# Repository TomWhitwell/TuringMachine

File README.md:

# TuringMachine Mark 2

Since it was launched in June 2012, the Turing Machine has become one of the most popular Eurorack DIY projects. It is a random looping sequencer that spits out basslines and melodies. It generates strings of random voltages that can be locked into looping sequences. 
These sequences can be allowed to slip, changing gradually over time. This module was inspired by the long history of shift register pseudorandom synth circuits, including the Triadex Muse, Buchla 266 Source of Uncertainly and Grant Richter’s Noisering.

[This video explains how the Turing Machine works.](https://www.youtube.com/watch?v=Le26BIqB8Y8)  

The 2016 revised Turing Machine has many improvements:  
- Rotary loop length switch 
- Pulse out
- Two boards, includes Backpack circuit to drive expanders (compatible with old Music Thing expanders)  
- Easier to build: a larger PCB in the same width, clock and noise circuits are more robust
- Noise level trimmer & reduced voltage in noise circuit to make circuit more robust with different noise transistors 
- Compatible with existing expanders 

*“I am interested in perceptible processes. I want to be able to hear the process happening throughout the music. To facilitate closely detailed listening a musical process should happen extremely gradually.”* Steve Reich, [Music as a Gradual Process](http://www.bussigel.com/systemsforplay/wp-content/uploads/2014/02/Reich_Gradual-Process.pdf), 1968. 

[Schematic](https://github.com/TomWhitwell/TuringMachine/blob/master/Collateral/PDF%20Schematics/TuringMachine2_Schematic_May2016.pdf)

Status:   
April 2016: Design files and Gerbers tested and prototyped successfully 

License:  
[CC-BY-SA](https://creativecommons.org/licenses/by-sa/3.0/)

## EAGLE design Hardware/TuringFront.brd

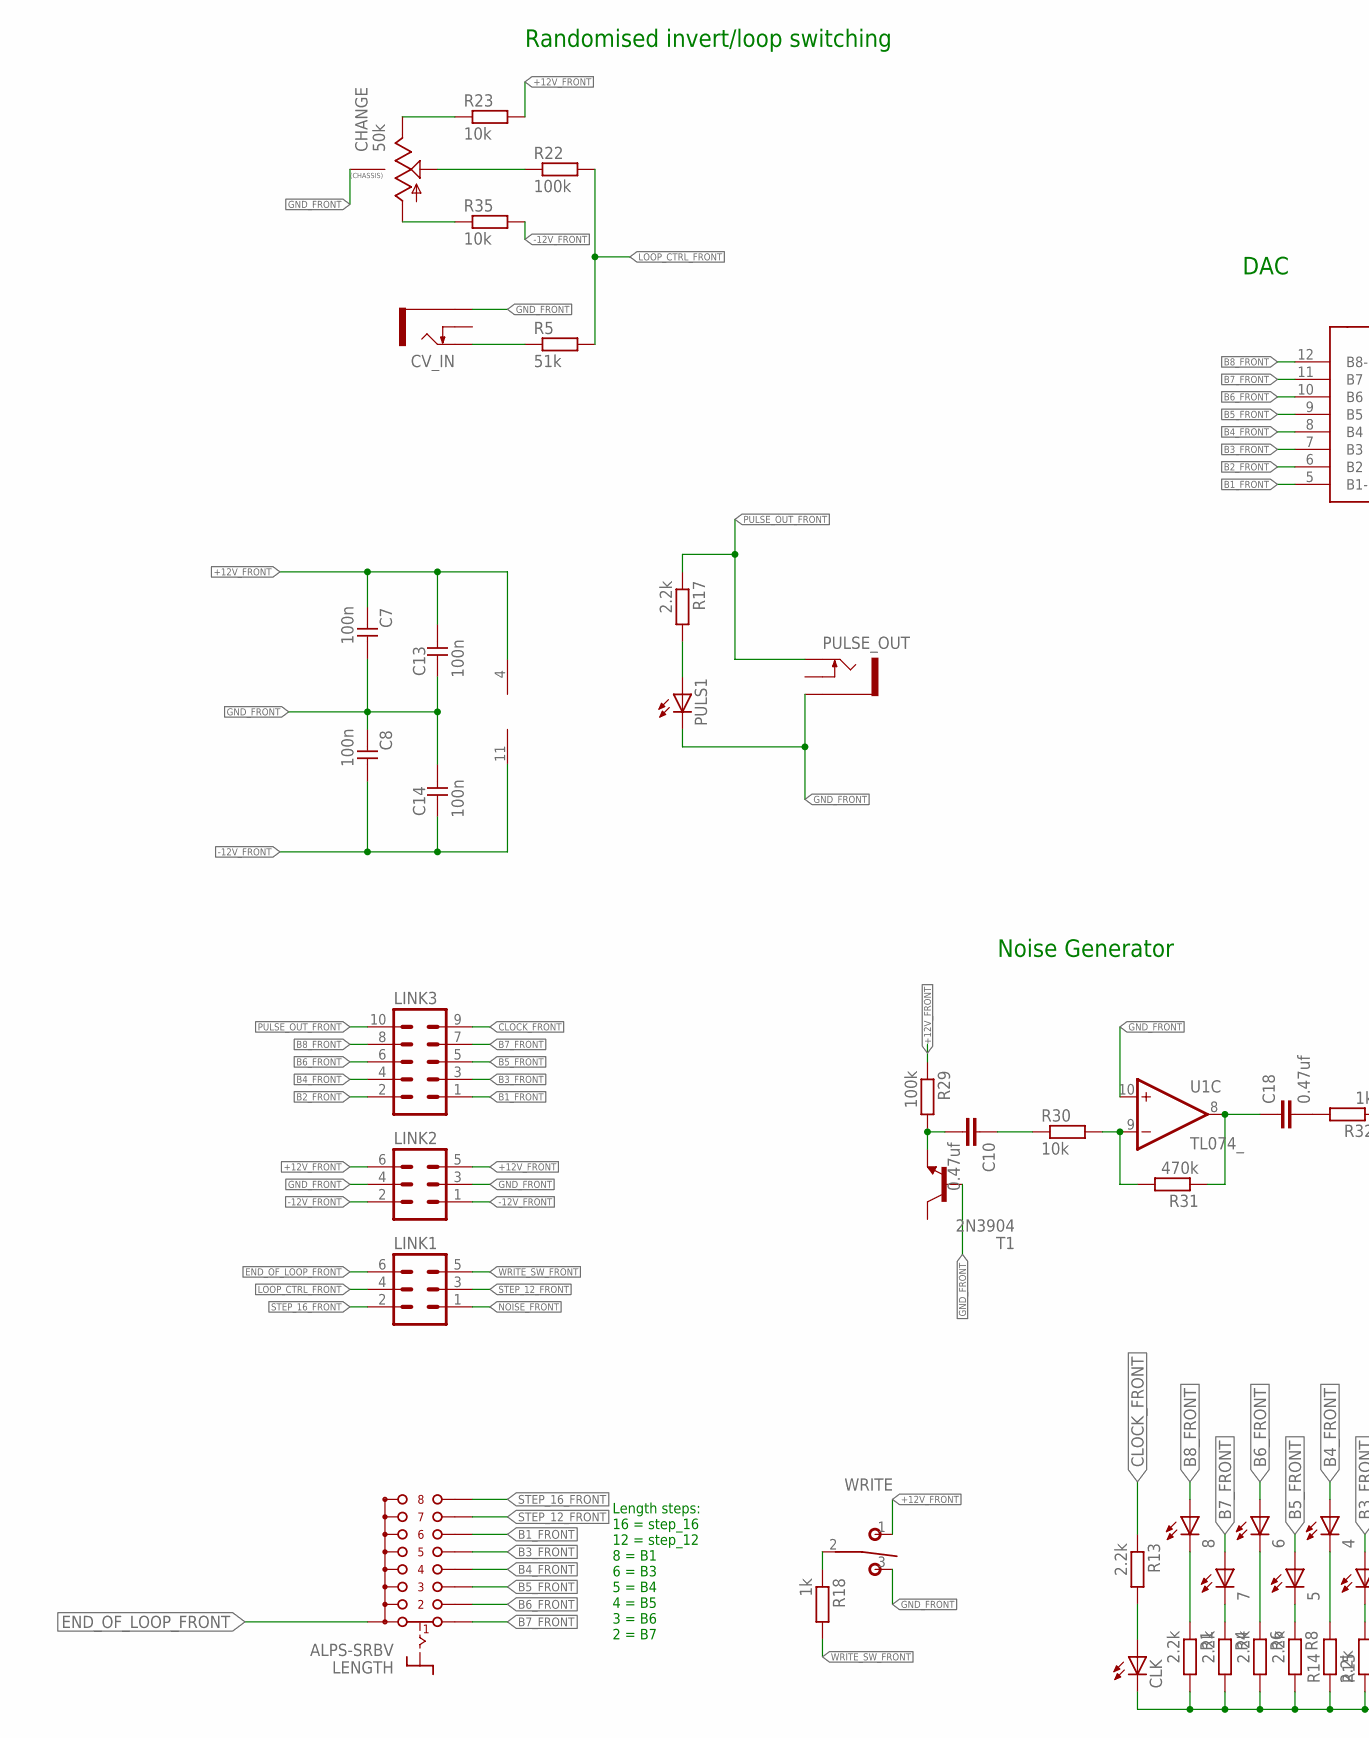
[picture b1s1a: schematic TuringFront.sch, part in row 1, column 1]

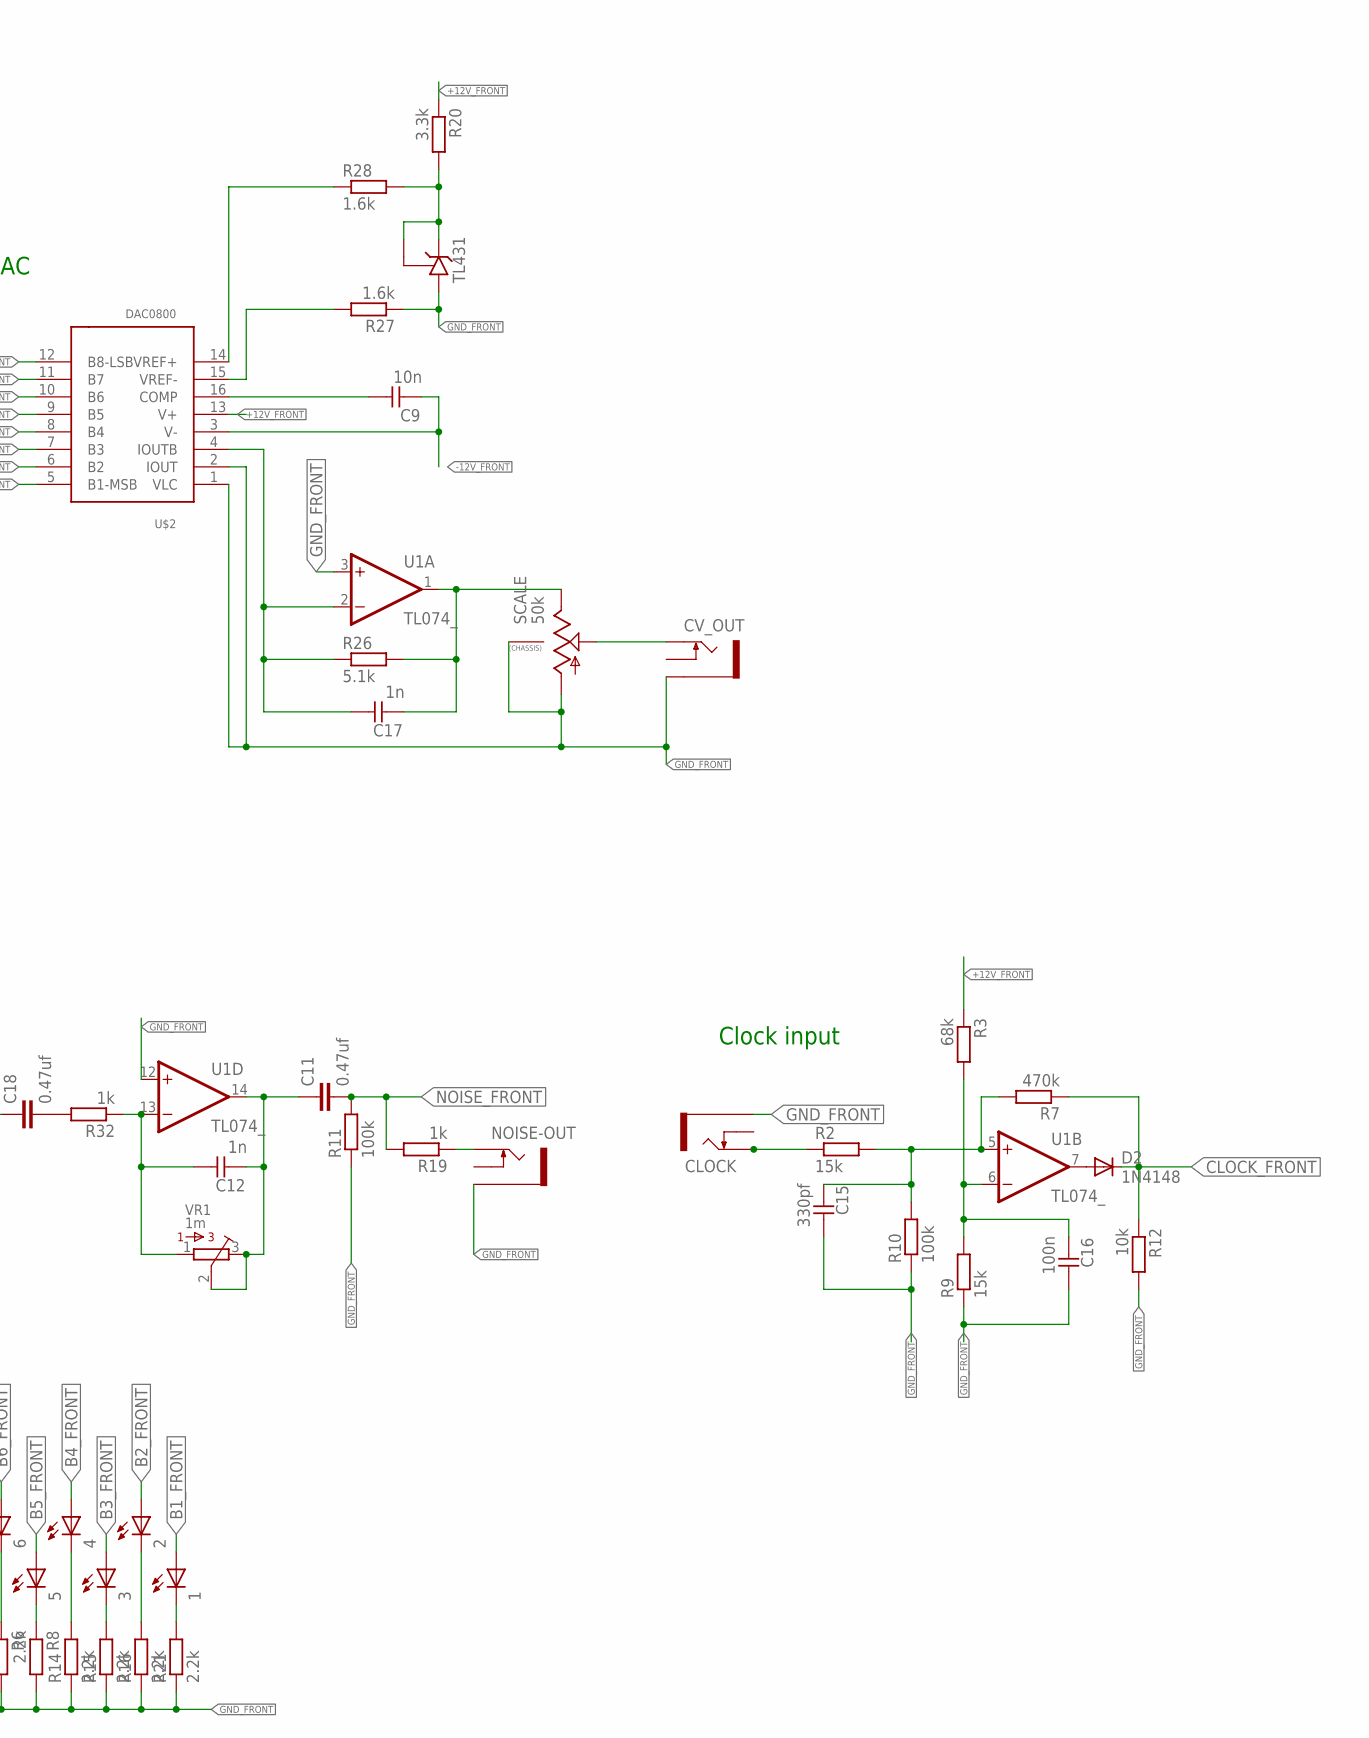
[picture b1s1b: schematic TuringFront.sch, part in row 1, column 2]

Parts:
1, 2, 3, 4, 5, 6, 7, 8: LED3MM
C7, C8, C13, C14, C16: 100n; C050-024X044
C9: 10n; C050-024X044
C10, C11, C18: 0.47uf; C050-035X075
C12, C17: 1n; C050-024X044
C15: 330pf; C050-024X044
CHANGE: 50k; 9MM_SNAP-IN_POT
CLK: LED3MM
CLOCK: THONKICONNNEW; WQP-PJ301M-12_JACK
CV_IN: THONKICONNNEW; WQP-PJ301M-12_JACK
CV_OUT: THONKICONNNEW; WQP-PJ301M-12_JACK
D2: 1N4148; DO35-7
LENGTH: ALPS-SRBV
LINK1, LINK2: MA03-2BACKSIDE
LINK3: 10PIN_BACKSIDE
NOISE-OUT: THONKICONNNEW; WQP-PJ301M-12_JACK
PULS1: LED3MM
PULSE_OUT: THONKICONNNEW; WQP-PJ301M-12_JACK
R1, R4, R6, R8, R13, R14, R15, R16, R17, R21: 2.2k; 0207/7
R2, R9: 15k; 0207/7
R3: 68k; 0207/7
R5: 51k; 0207/7
R7, R31: 470k; 0207/7
R10, R22, R29: 100k; 0207/7
R11: 100k; 7MM_RESISTOR
R12, R23, R30, R35: 10k; 0207/7
R18, R19, R32: 1k; 0207/7
R20: 3.3k; 0207/7
R26: 5.1k; 0207/7
R27, R28: 1.6k; 0207/7
SCALE: 50k; 9MM_SNAP-IN_POT
T1: 2N3904; TO92
TL431: TL431CLP; TO92-CLP
U1: TL074_; DIL14
U$2: DAC0800; DIL16
VR1: 1m; BOURNS_3362P_TRIMMER
WRITE: T-80-T-SPDT-ON-OFF-ON; M9040P

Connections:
+12V_FRONT: C7.2, C13.1, LINK2.5, LINK2.6, R3.1, R20.1, R23.2, R29.1, U1.4 (V+), U$2.13 (V+), WRITE.1 (O)
-12V_FRONT: C8.1, C9.2, C14.2, LINK2.1, LINK2.2, R35.2, U1.11 (V-), U$2.3 (V-)
B1_FRONT: 1.A, LENGTH.F (6), LINK3.1, U$2.5 (B1-MSB)
B2_FRONT: 2.A, LINK3.2, U$2.6 (B2)
B3_FRONT: 3.A, LENGTH.E (5), LINK3.3, U$2.7 (B3)
B4_FRONT: 4.A, LENGTH.D (4), LINK3.4, U$2.8 (B4)
B5_FRONT: 5.A, LENGTH.C (3), LINK3.5, U$2.9 (B5)
B6_FRONT: 6.A, LENGTH.B (2), LINK3.6, U$2.10 (B6)
B7_FRONT: 7.A, LENGTH.A (1), LINK3.7, U$2.11 (B7)
B8_FRONT: 8.A, LINK3.8, U$2.12 (B8-LSB)
CLOCK_FRONT: D2.C, LINK3.9, R7.1, R12.1, R13.1
END_OF_LOOP_FRONT: LENGTH.COM (A), LENGTH.COM2 (A), LINK1.6
GND_FRONT: C7.1, C8.2, C13.2, C14.1, C15.1, C16.1, CHANGE.CHASSIS2, CLK.K (C), CLOCK.P$3_SLEEVE (SLEEVE), CV_IN.P$3_SLEEVE (SLEEVE), CV_OUT.P$3_SLEEVE (SLEEVE), LINK2.3, LINK2.4, NOISE-OUT.P$3_SLEEVE (SLEEVE), PULS1.K (C), PULSE_OUT.P$3_SLEEVE (SLEEVE), R1.2, R4.2, R6.2, R8.2, R9.1, R10.1, R11.1, R12.2, R14.1, R15.1, R16.1, R21.1, R27.1, SCALE.1 (A), SCALE.CHASSIS2, T1.2 (B), TL431.A, U1.3 (+IN), U1.10 (+IN), U1.12 (+IN), U$2.1 (VLC), U$2.2 (IOUT), WRITE.3 (S)
LOOP_CTRL_FRONT: LINK1.4, R5.2, R22.2
MAIN_OUT: C17.2, R26.2, SCALE.3 (E), U1.1 (OUT)
unnamed: CLOCK.P$1_TIP (TIP), R2.1
unnamed: CV_IN.P$1_TIP (TIP), R5.1
unnamed: C15.2, R2.2, R7.2, R10.2, U1.5 (+IN)
unnamed: PULS1.A, R17.2
unnamed: D2.A, U1.7 (OUT)
unnamed: C18.2, R32.2
unnamed: R18.1, WRITE.2
unnamed: C16.2, R3.2, R9.2, U1.6 (-IN)
unnamed: C17.1, R26.1, U1.2 (-IN), U$2.4 (IOUTB)
unnamed: CLK.A, R13.2
unnamed: C10.2, R29.2, T1.3 (E)
unnamed: R20.2, R28.2, TL431.C, TL431.R
unnamed: C10.1, R30.1
unnamed: R30.2, R31.2, U1.9 (-IN)
unnamed: C18.1, R31.1, U1.8 (OUT)
unnamed: R27.2, U$2.15 (VREF-)
unnamed: C9.1, U$2.16 (COMP)
unnamed: R28.1, U$2.14 (VREF+)
unnamed: C12.1, R32.1, U1.13 (-IN), VR1.1
unnamed: 8.K (C), R1.1
unnamed: 7.K (C), R4.1
unnamed: 6.K (C), R6.1
unnamed: 5.K (C), R8.1
unnamed: 4.K (C), R14.2
unnamed: 3.K (C), R15.2
unnamed: 2.K (C), R16.2
unnamed: 1.K (C), R21.2
unnamed: CV_OUT.P$1_TIP (TIP), SCALE.2 (S)
unnamed: NOISE-OUT.P$1_TIP (TIP), R19.1
unnamed: C11.1, C12.2, U1.14 (OUT), VR1.2, VR1.3
unnamed: CHANGE.2 (S), R22.1
unnamed: CHANGE.3 (E), R23.1
unnamed: CHANGE.1 (A), R35.1
NOISE_FRONT: C11.2, LINK1.1, R11.2, R19.2
PULSE_OUT_FRONT: LINK3.10, PULSE_OUT.P$1_TIP (TIP), R17.1
STEP_12_FRONT: LENGTH.G (7), LINK1.3
STEP_16_FRONT: LENGTH.H (8), LINK1.2
WRITE_SW_FRONT: LINK1.5, R18.2

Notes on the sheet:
Randomised invert/loop switching
Length steps: 16 = step_16 12 = step_12 8 = B1 6 = B3 5 = B4 4 = B5 3 = B6 2 = B7
Noise Generator
Clock input
DAC

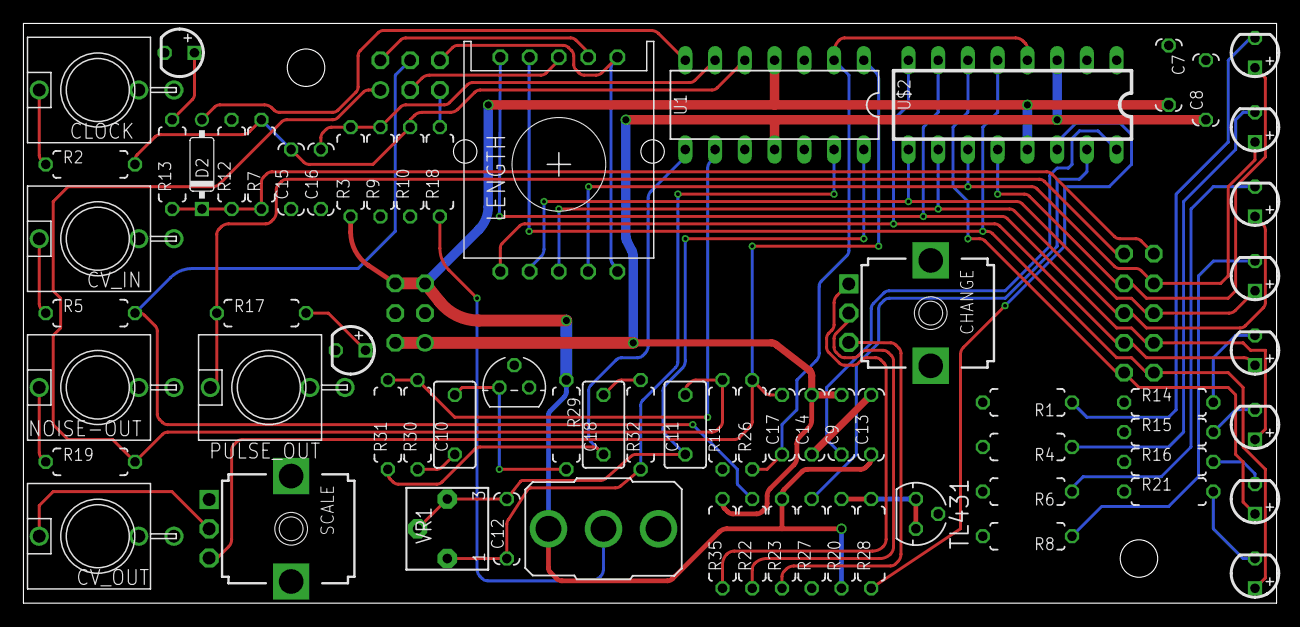
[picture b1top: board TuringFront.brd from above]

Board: 4 copper layers, 107.0 x 49.5 mm, 73 parts (0 on the bottom side), 53 nets.

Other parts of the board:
U$4, U$5: MOUNTING_HOLE

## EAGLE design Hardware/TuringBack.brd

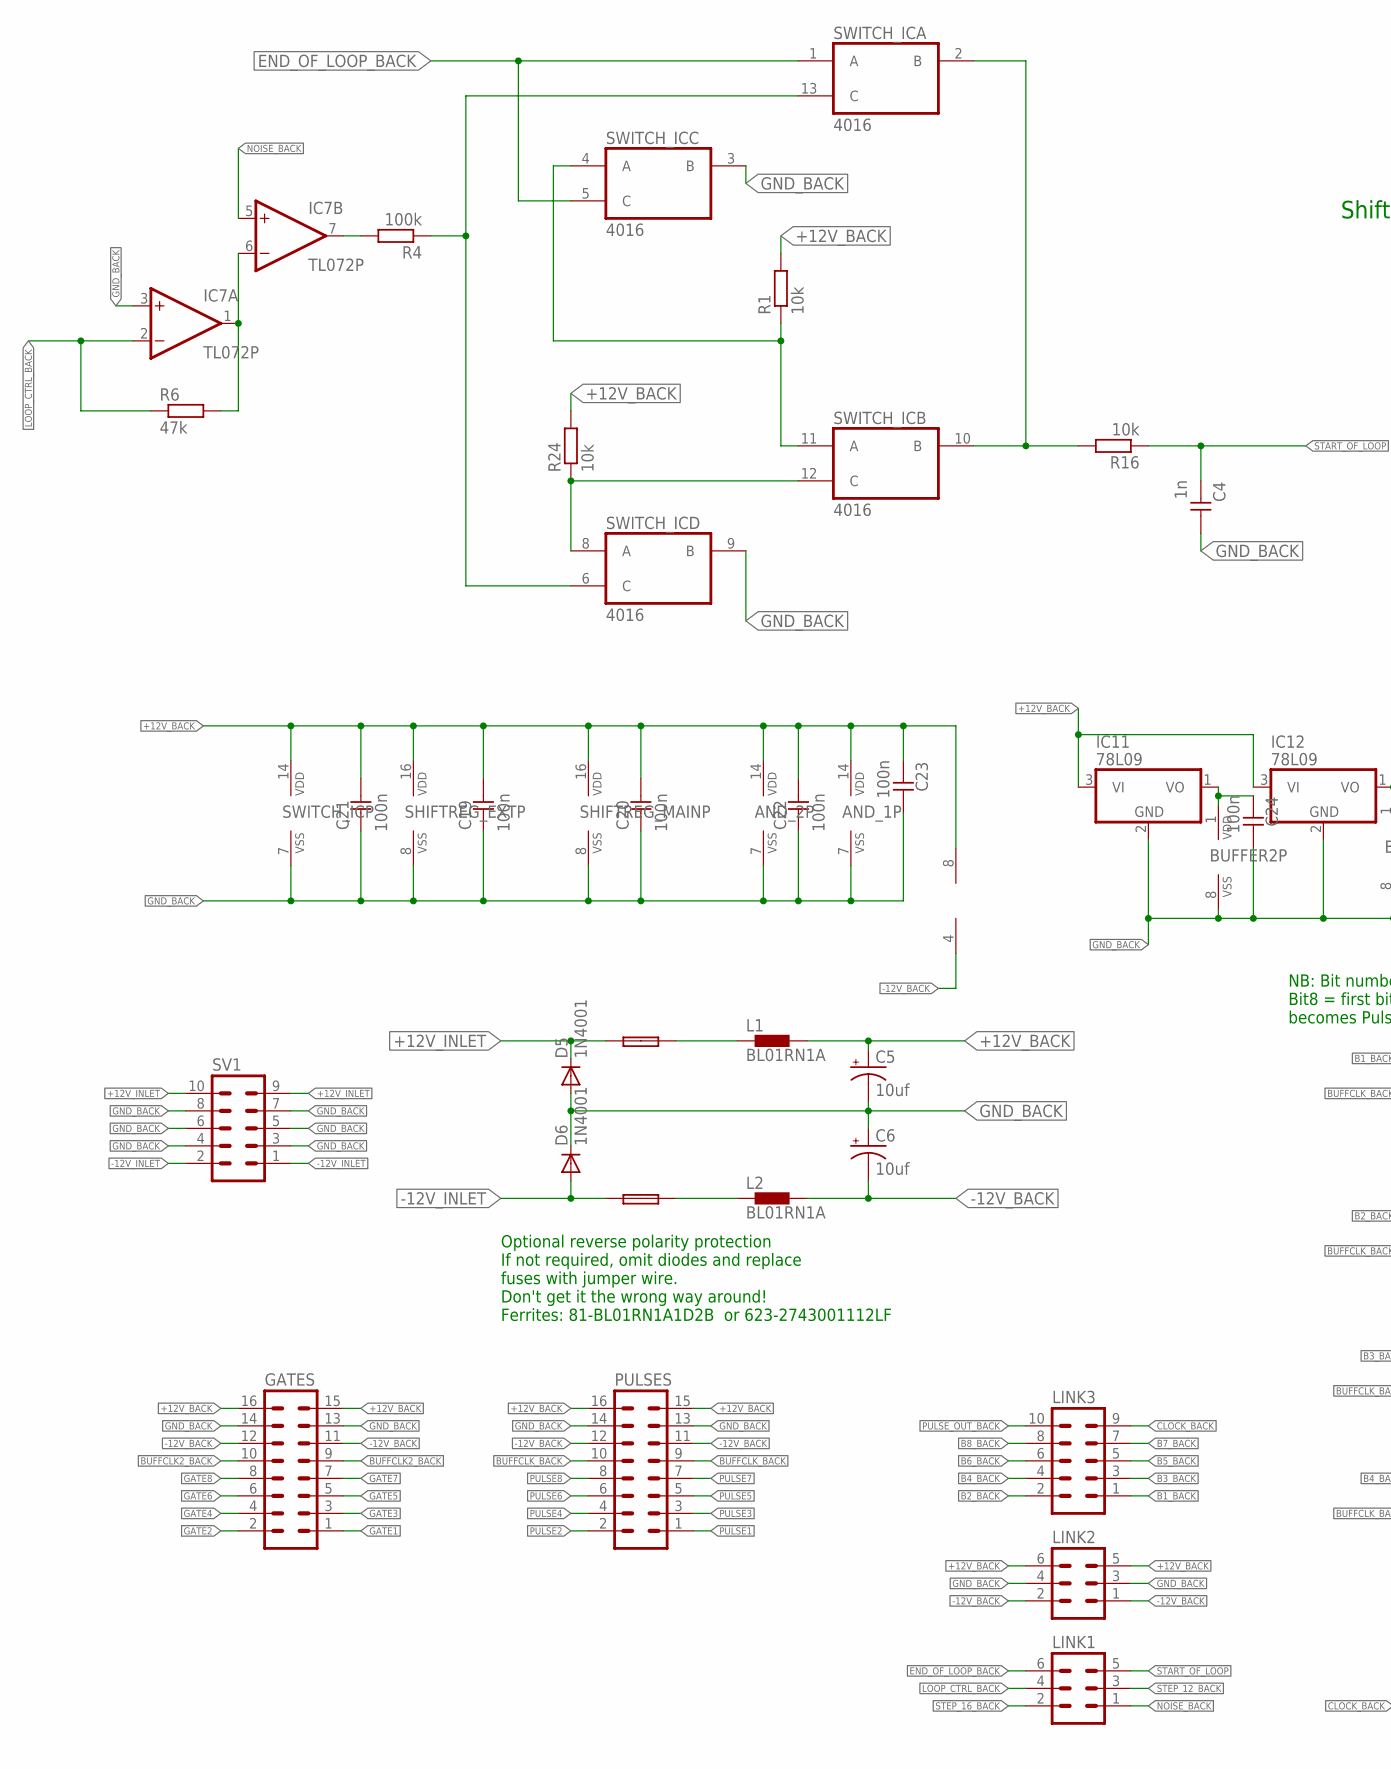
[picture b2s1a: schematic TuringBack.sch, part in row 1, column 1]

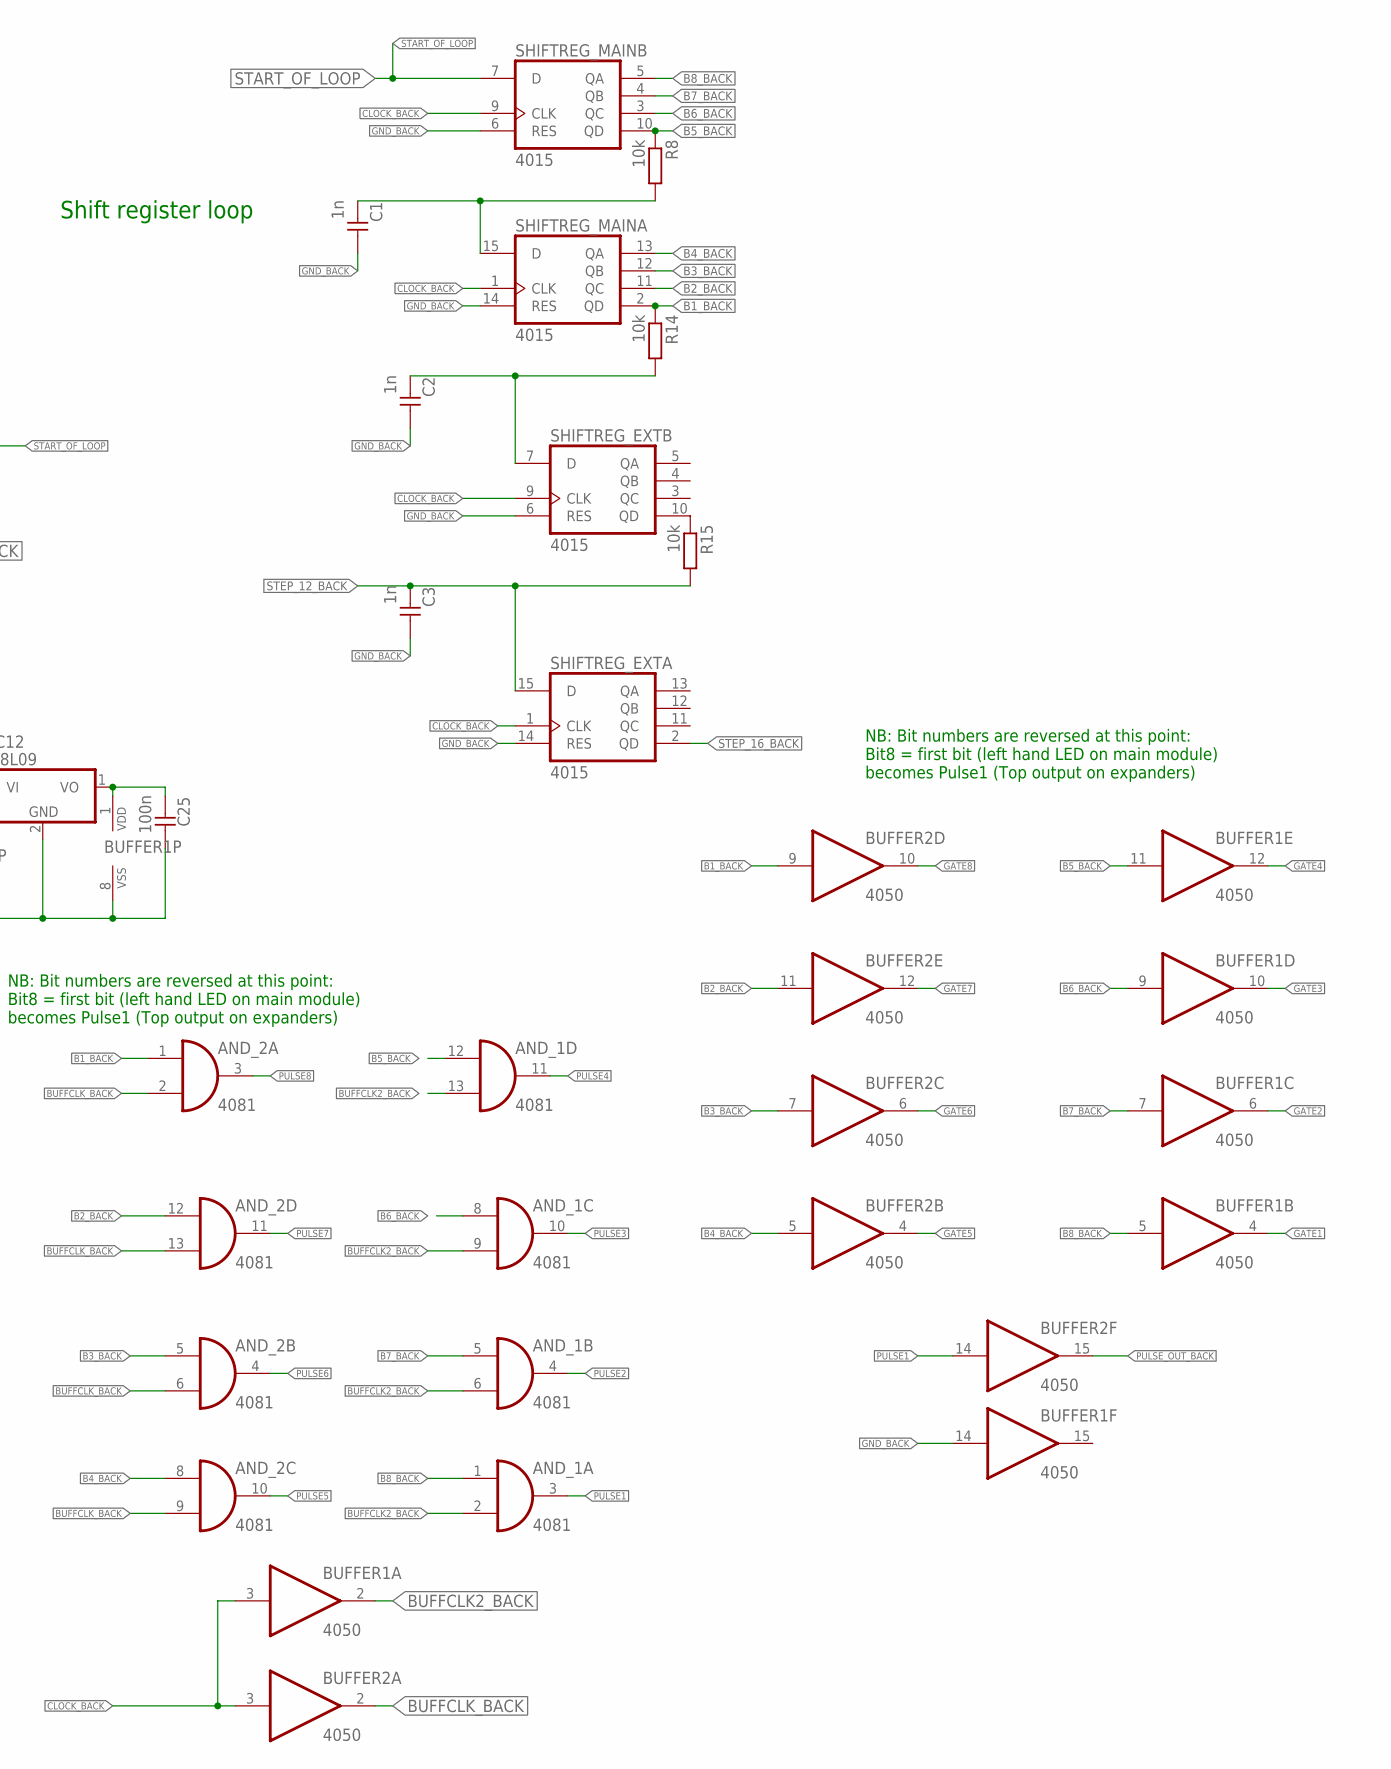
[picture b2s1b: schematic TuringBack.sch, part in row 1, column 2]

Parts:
+FUSE: +FUSE; C050H075X075
-FUSE: -FUSE; C050H075X075
AND_1, AND_2: 4081; DIL14
BUFFER1, BUFFER2: 4050; DIL16
C1, C2, C3, C4: 1n; C050-024X044
C5, C6: 10uf; CPOL-RADIAL-10UF-25V
C19, C20, C21, C22, C23, C24, C25: 100n; C050-024X044
D5, D6: 1N4001; DO41-10
GATES: MA08-2
IC7: TL072P; DIL08
IC11, IC12: 78L09; TO92
L1, L2: BL01RN1A
LINK1, LINK2: MA03-2
LINK3: MA05-2
PULSES: MA08-2
R1, R8, R14, R15, R16, R24: 10k; 0207/7
R4: 100k; 0207/7
R6: 47k; 0207/7
SHIFTREG_EXT: 4015; DIL16
SHIFTREG_MAIN: 4015; DIL16
SV1: 10_PIN_HEADER; MA05-2
SWITCH_IC: 4016; DIL14

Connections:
+9V_1: BUFFER2.1 (VDD), C24.2, IC11.1 (VO)
+9V_2: BUFFER1.1 (VDD), C25.2, IC12.1 (VO)
+12V_BACK: AND_1.14 (VDD), AND_2.14 (VDD), C5.1 (+), C19.1, C20.1, C21.1, C22.1, C23.2, GATES.15, GATES.16, IC7.8 (V+), IC11.3 (VI), IC12.3 (VI), L1.2, LINK2.5, LINK2.6, PULSES.15, PULSES.16, R1.2, R24.2, SHIFTREG_EXT.16 (VDD), SHIFTREG_MAIN.16 (VDD), SWITCH_IC.14 (VDD)
+12V_INLET: +FUSE.1, D5.C, SV1.9, SV1.10
-12V_BACK: C6.2 (-), GATES.11, GATES.12, IC7.4 (V-), L2.2, LINK2.1, LINK2.2, PULSES.11, PULSES.12
-12V_INLET: -FUSE.1, D6.A, SV1.1, SV1.2
B1_BACK: AND_2.1 (I0), BUFFER2.9 (I), LINK3.1, R14.1, SHIFTREG_MAIN.2 (QD)
B2_BACK: AND_2.12 (I0), BUFFER2.11 (I), LINK3.2, SHIFTREG_MAIN.11 (QC)
B3_BACK: AND_2.5 (I0), BUFFER2.7 (I), LINK3.3, SHIFTREG_MAIN.12 (QB)
B4_BACK: AND_2.8 (I0), BUFFER2.5 (I), LINK3.4, SHIFTREG_MAIN.13 (QA)
B5_BACK: AND_1.12 (I0), BUFFER1.11 (I), LINK3.5, R8.1, SHIFTREG_MAIN.10 (QD)
B6_BACK: AND_1.8 (I0), BUFFER1.9 (I), LINK3.6, SHIFTREG_MAIN.3 (QC)
B7_BACK: AND_1.5 (I0), BUFFER1.7 (I), LINK3.7, SHIFTREG_MAIN.4 (QB)
B8_BACK: AND_1.1 (I0), BUFFER1.5 (I), LINK3.8, SHIFTREG_MAIN.5 (QA)
BUFFCLK2_BACK: AND_1.2 (I1), AND_1.6 (I1), AND_1.9 (I1), AND_1.13 (I1), BUFFER1.2 (O), GATES.9, GATES.10
BUFFCLK_BACK: AND_2.2 (I1), AND_2.6 (I1), AND_2.9 (I1), AND_2.13 (I1), BUFFER2.2 (O), PULSES.9, PULSES.10
CLOCK_BACK: BUFFER1.3 (I), BUFFER2.3 (I), LINK3.9, SHIFTREG_EXT.1 (CLK), SHIFTREG_EXT.9 (CLK), SHIFTREG_MAIN.1 (CLK), SHIFTREG_MAIN.9 (CLK)
END_OF_LOOP_BACK: LINK1.6, SWITCH_IC.1 (A), SWITCH_IC.5 (C)
GATE1: BUFFER1.4 (O), GATES.1
GATE2: BUFFER1.6 (O), GATES.2
GATE3: BUFFER1.10 (O), GATES.3
GATE4: BUFFER1.12 (O), GATES.4
GATE5: BUFFER2.4 (O), GATES.5
GATE6: BUFFER2.6 (O), GATES.6
GATE7: BUFFER2.12 (O), GATES.7
GATE8: BUFFER2.10 (O), GATES.8
GND_BACK: AND_1.7 (VSS), AND_2.7 (VSS), BUFFER1.8 (VSS), BUFFER1.14 (I), BUFFER2.8 (VSS), C1.1, C2.1, C3.1, C4.1, C5.2 (-), C6.1 (+), C19.2, C20.2, C21.2, C22.2, C23.1, C24.1, C25.1, D5.A, D6.C, GATES.13, GATES.14, IC7.3 (+IN), IC11.2 (GND), IC12.2 (GND), LINK2.3, LINK2.4, PULSES.13, PULSES.14, SHIFTREG_EXT.6 (RES), SHIFTREG_EXT.8 (VSS), SHIFTREG_EXT.14 (RES), SHIFTREG_MAIN.6 (RES), SHIFTREG_MAIN.8 (VSS), SHIFTREG_MAIN.14 (RES), SV1.3, SV1.4, SV1.5, SV1.6, SV1.7, SV1.8, SWITCH_IC.3 (B), SWITCH_IC.7 (VSS), SWITCH_IC.9 (B)
LOOP_CTRL_BACK: IC7.2 (-IN), LINK1.4, R6.1
unnamed: IC7.7 (OUT), R4.2
unnamed: R4.1, SWITCH_IC.6 (C), SWITCH_IC.13 (C)
unnamed: R1.1, SWITCH_IC.4 (A), SWITCH_IC.11 (A)
unnamed: IC7.1 (OUT), IC7.6 (-IN), R6.2
unnamed: C1.2, R8.2, SHIFTREG_MAIN.15 (D)
unnamed: R15.1, SHIFTREG_EXT.10 (QD)
unnamed: R16.2, SWITCH_IC.2 (B), SWITCH_IC.10 (B)
unnamed: C2.2, R14.2, SHIFTREG_EXT.7 (D)
unnamed: +FUSE.2, L1.1
unnamed: -FUSE.2, L2.1
unnamed: R24.1, SWITCH_IC.8 (A), SWITCH_IC.12 (C)
NOISE_BACK: IC7.5 (+IN), LINK1.1
PULSE1: AND_1.3 (O), BUFFER2.14 (I), PULSES.1
PULSE2: AND_1.4 (O), PULSES.2
PULSE3: AND_1.10 (O), PULSES.3
PULSE4: AND_1.11 (O), PULSES.4
PULSE5: AND_2.10 (O), PULSES.5
PULSE6: AND_2.4 (O), PULSES.6
PULSE7: AND_2.11 (O), PULSES.7
PULSE8: AND_2.3 (O), PULSES.8
PULSE_OUT_BACK: BUFFER2.15 (O), LINK3.10
START_OF_LOOP: C4.2, LINK1.5, R16.1, SHIFTREG_MAIN.7 (D)
STEP_12_BACK: C3.2, LINK1.3, R15.2, SHIFTREG_EXT.15 (D)
STEP_16_BACK: LINK1.2, SHIFTREG_EXT.2 (QD)

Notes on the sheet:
Shift register loop
Optional reverse polarity protection If not required, omit diodes and replace fuses with jumper wire. Don't get it the wrong way around! Ferrites: 81-BL01RN1A1D2B or 623-2743001112LF
NB: Bit numbers are reversed at this point: Bit8 = first bit (left hand LED on main module) becomes Pulse1 (Top output on expanders)

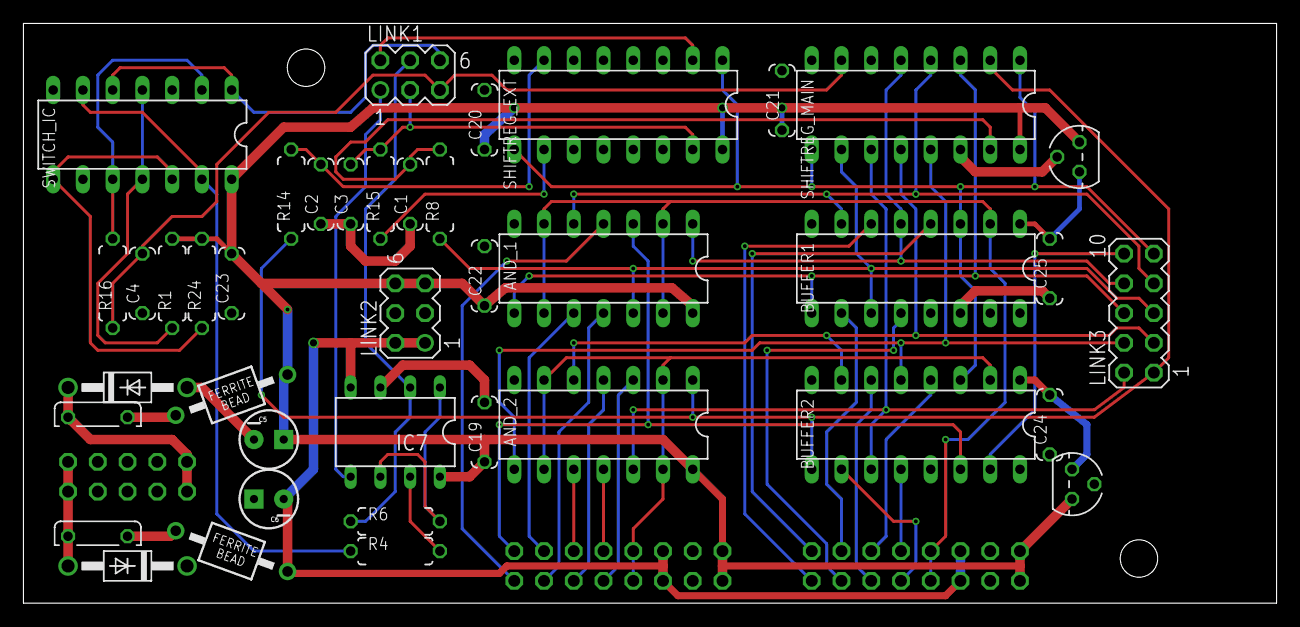
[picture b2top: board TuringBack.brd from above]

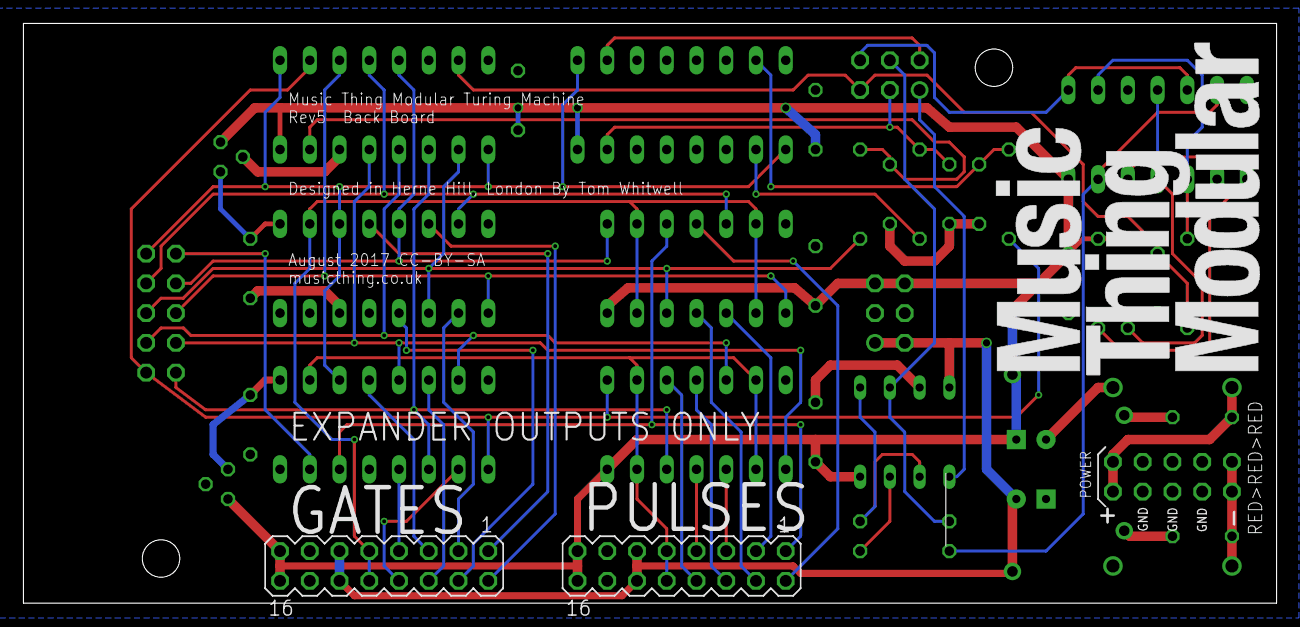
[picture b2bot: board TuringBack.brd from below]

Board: 4 copper layers, 107.0 x 49.5 mm, 45 parts (3 on the bottom side), 52 nets.

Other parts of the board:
U$4, U$5: MOUNTING_HOLE

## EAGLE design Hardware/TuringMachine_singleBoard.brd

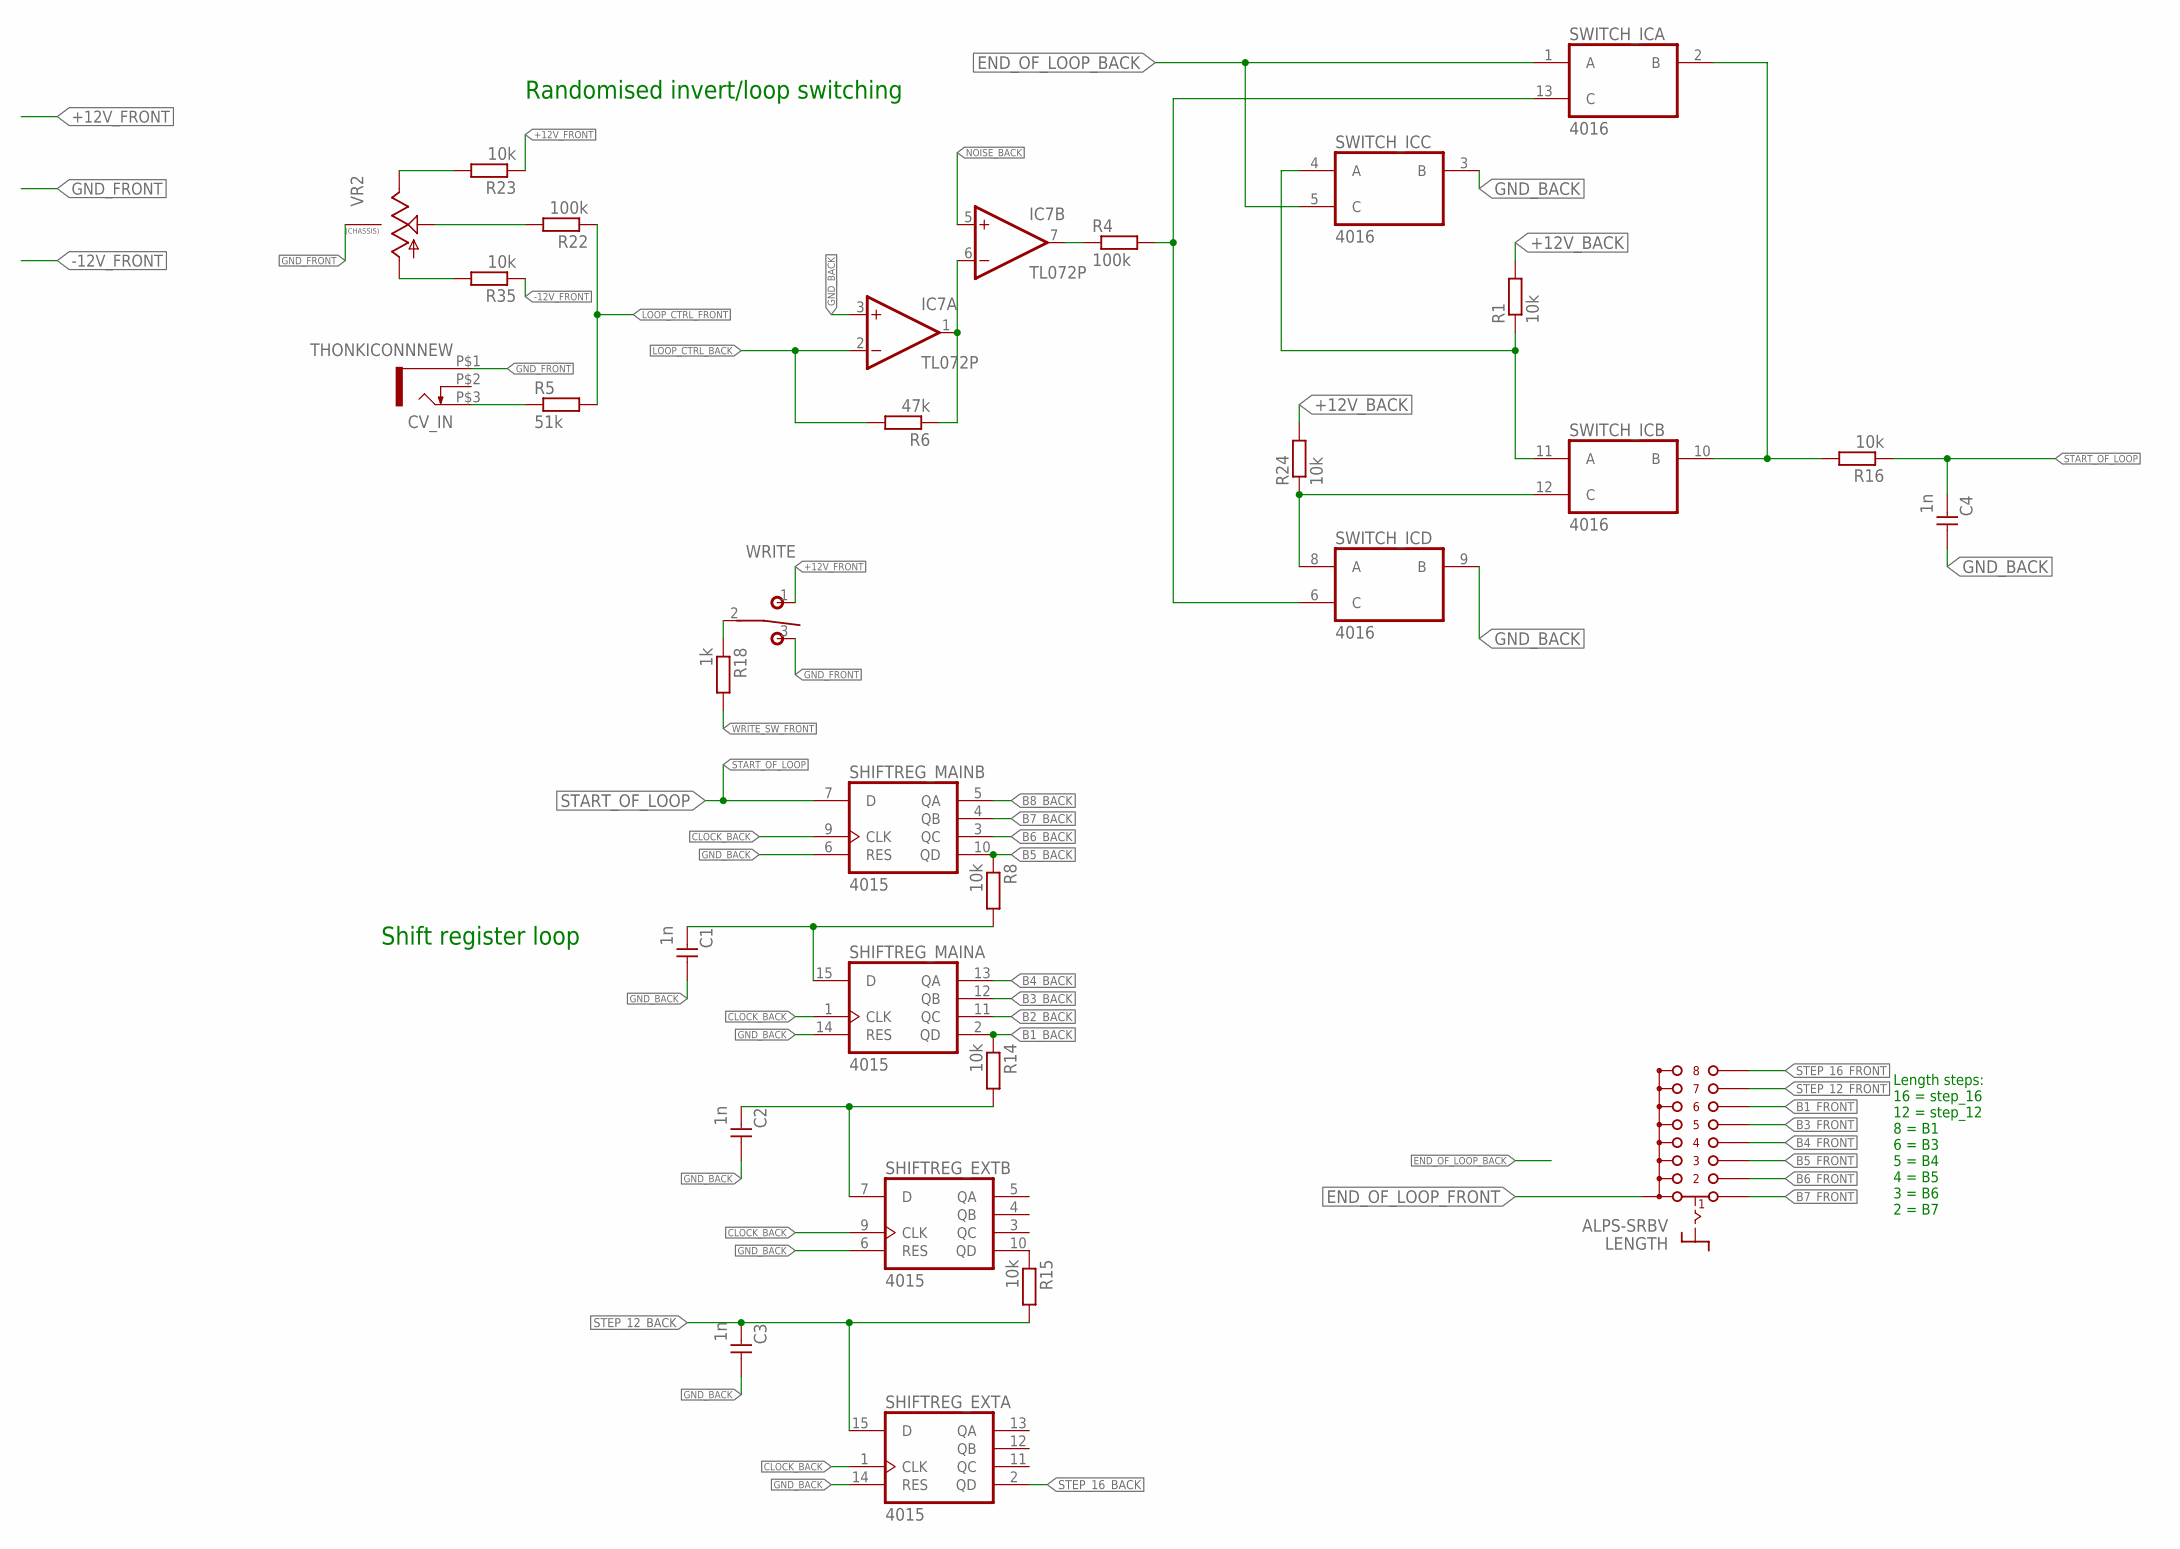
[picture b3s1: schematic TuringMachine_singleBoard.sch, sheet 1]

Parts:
C1, C2, C3, C4: 1n; C050-024X044
CV_IN: THONKICONNNEW; WQP-PJ301M-12_JACK
IC7: TL072P; DIL08
LENGTH: ALPS-SRBV
R1, R8, R14, R15, R16, R23, R24, R35: 10k; 0207/7
R4, R22: 100k; 0207/7
R5: 51k; 0207/7
R6: 47k; 0207/7
R18: 1k; 0207/7
SHIFTREG_EXT: 4015; DIL16
SHIFTREG_MAIN: 4015; DIL16
SWITCH_IC: 4016; DIL14
VR2: 9MM_SNAP-IN_POT_CHASSIS; 9MM_SNAP-IN_POT
WRITE: T-80-T-SPDT-ON-OFF-ON; M9040P

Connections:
+12V_BACK: R1.2, R24.2; also elsewhere on the board
+12V_FRONT: R23.1, WRITE.1 (O); also elsewhere on the board
-12V_FRONT: R35.1; also elsewhere on the board
B1_BACK: R14.1, SHIFTREG_MAIN.2 (QD); also elsewhere on the board
B1_FRONT: LENGTH.F (6); also elsewhere on the board
B2_BACK: SHIFTREG_MAIN.11 (QC); also elsewhere on the board
B3_BACK: SHIFTREG_MAIN.12 (QB); also elsewhere on the board
B3_FRONT: LENGTH.E (5); also elsewhere on the board
B4_BACK: SHIFTREG_MAIN.13 (QA); also elsewhere on the board
B4_FRONT: LENGTH.D (4); also elsewhere on the board
B5_BACK: R8.1, SHIFTREG_MAIN.10 (QD); also elsewhere on the board
B5_FRONT: LENGTH.C (3); also elsewhere on the board
B6_BACK: SHIFTREG_MAIN.3 (QC); also elsewhere on the board
B6_FRONT: LENGTH.B (2); also elsewhere on the board
B7_BACK: SHIFTREG_MAIN.4 (QB); also elsewhere on the board
B7_FRONT: LENGTH.A (1); also elsewhere on the board
B8_BACK: SHIFTREG_MAIN.5 (QA); also elsewhere on the board
CLOCK_BACK: SHIFTREG_EXT.1 (CLK), SHIFTREG_EXT.9 (CLK), SHIFTREG_MAIN.1 (CLK), SHIFTREG_MAIN.9 (CLK); also elsewhere on the board
END_OF_LOOP_BACK: SWITCH_IC.1 (A), SWITCH_IC.5 (C); also elsewhere on the board
END_OF_LOOP_FRONT: LENGTH.COM (A), LENGTH.COM2 (A); also elsewhere on the board
GND_BACK: C1.1, C2.1, C3.1, C4.1, IC7.3 (+IN), SHIFTREG_EXT.6 (RES), SHIFTREG_EXT.14 (RES), SHIFTREG_MAIN.6 (RES), SHIFTREG_MAIN.14 (RES), SWITCH_IC.3 (B), SWITCH_IC.9 (B); also elsewhere on the board
GND_FRONT: CV_IN.P$1 (5), VR2.M1, VR2.M2, WRITE.3 (S); also elsewhere on the board
LOOP_CTRL_BACK: IC7.2 (-IN), R4.2, R6.2, SWITCH_IC.6 (C), SWITCH_IC.13 (C); also elsewhere on the board
LOOP_CTRL_FRONT: R5.2, R22.1; also elsewhere on the board
unnamed: IC7.7 (OUT), R4.1
unnamed: CV_IN.P$3 (3), R5.1
unnamed: R1.1, SWITCH_IC.4 (A), SWITCH_IC.11 (A)
unnamed: IC7.1 (OUT), IC7.6 (-IN), R6.1
unnamed: C1.2, R8.2, SHIFTREG_MAIN.15 (D)
unnamed: R18.1, WRITE.2
unnamed: R15.1, SHIFTREG_EXT.10 (QD)
unnamed: R16.2, SWITCH_IC.2 (B), SWITCH_IC.10 (B)
unnamed: C2.2, R14.2, SHIFTREG_EXT.7 (D)
unnamed: R22.2, VR2.2 (S)
unnamed: R24.1, SWITCH_IC.8 (A), SWITCH_IC.12 (C)
unnamed: R23.2, VR2.3 (E)
unnamed: R35.2, VR2.1 (A)
NOISE_BACK: IC7.5 (+IN); also elsewhere on the board
START_OF_LOOP: C4.2, R16.1, SHIFTREG_MAIN.7 (D); also elsewhere on the board
STEP_12_BACK: C3.2, R15.2, SHIFTREG_EXT.15 (D); also elsewhere on the board
STEP_12_FRONT: LENGTH.G (7); also elsewhere on the board
STEP_16_BACK: SHIFTREG_EXT.2 (QD); also elsewhere on the board
STEP_16_FRONT: LENGTH.H (8); also elsewhere on the board
WRITE_SW_FRONT: R18.2; also elsewhere on the board

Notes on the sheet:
Randomised invert/loop switching
Shift register loop
Length steps: 16 = step_16 12 = step_12 8 = B1 6 = B3 5 = B4 4 = B5 3 = B6 2 = B7

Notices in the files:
Hardware/TuringBack.brd:
August 2017 CC-BY-SA
Hardware/TuringFront.brd:
January 2018 CC-BY-SA
parts and their libraries:
SparkFun-Passives: Licensing: CC v3.0 Share-Alike You are welcome to use this library for commercial purposes.
